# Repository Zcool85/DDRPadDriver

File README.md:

# Introduction

Projet de création d'un tapis de dance pour le jeu Dance Dance Revolution.

Ce tapis est utilisable sur un PC pour des jeux comme `Stepmania` ou `Outfox`, mais également sur
console Playstation (1 et 2).

Le firmware est à base de microcontroller AVR ©.

Les touches du tapis peuvent être illuminées. Dans ce cas, il convient d'ajouter une alimentation externe pour les LED (CAO `Power_Supply`). Cette alimentation est inutile si le tapis est utilisé sans éclairage.

## Licence

Le présent projet est sous licence MIT (Cf. [License](LICENSE.md)).

ATTENTION : Le Firmware utilise une librairie tierce V-USB pour la connexion USB vers un PC.
Cette librairie est soumie à une licnece GNU General Public License Version 2 (GPL). Merci
de consulter a license de cette bibliothèque en cas de modification.

Cf. [Librairie V-USB](https://obdev.at/products/vusb/index.html).

## Organisation du repo

Le répertoire `CAD` contient les fichiers de CAO des diférents composants :
- `Power_Supply` : Fichier CAO utilisé pour le bloc d'alimentation des tapis
- `For_Childrens` : Fichier CAO utilisé pour créer un tapis à la taille d'un enfant (~6ans)
- `For_Adults` : Fichier CAO utilisé pour créer un tapis pour adulte
- `Fonts` : Répertoire contenant les fonts utilisées par les fichiers de CAO

Le répertoire `Schematics` contient le shéma du circuit électronique du tapis.

Le répertoire `Datasheets` contient tous les datasheets des composants utilisés par le circuit électronique.

Le répertoire `Firmware` contient le code complet du firmware du microcontroller présent dans le circtui électronique.

Le répertoire `Documentation` Contient un peu de documentation permettant de comprendre comment fonctionne les trames d'une manette PS2.

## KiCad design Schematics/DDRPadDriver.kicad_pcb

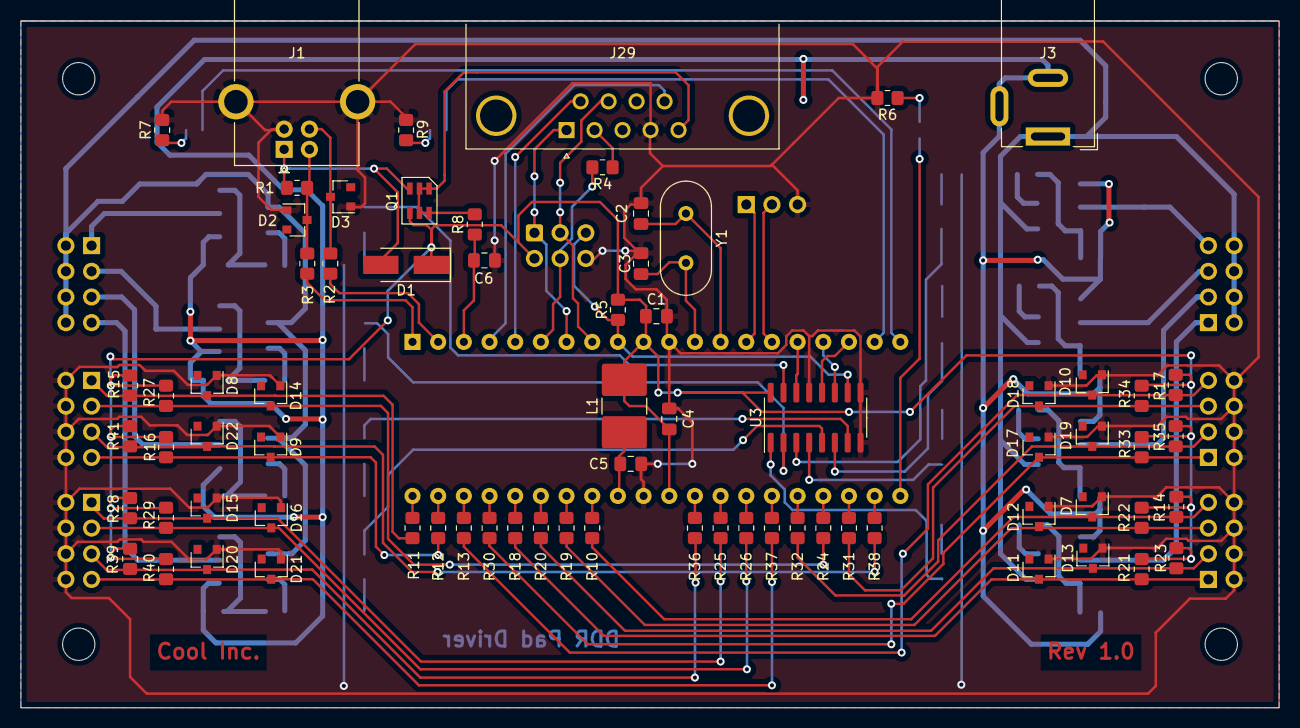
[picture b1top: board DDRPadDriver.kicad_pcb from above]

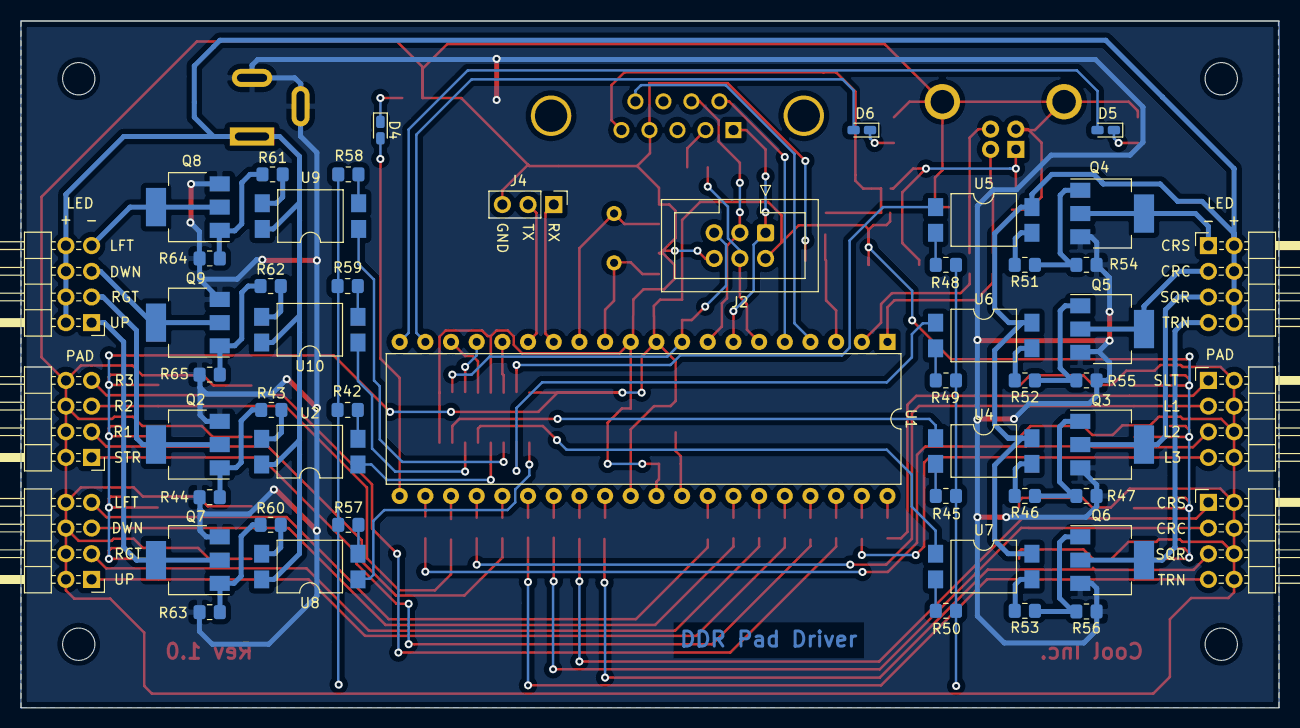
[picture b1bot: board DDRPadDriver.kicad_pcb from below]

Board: 2 copper layers, 124.5 x 67.9 mm, 129 parts (52 on the bottom side), 104 nets.

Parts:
C1: 4.7uF; C_0805_2012Metric_Pad1.18x1.45mm_HandSolder
C2, C3: 10pF; C_0805_2012Metric_Pad1.18x1.45mm_HandSolder
C4, C5, C6: 0.1uF; C_0805_2012Metric_Pad1.18x1.45mm_HandSolder
D1: SS12; D_SMA_Handsoldering
D2, D3: 3V6; D_SOT-23_ANK
D4, D5, D6: LED; LED_0603_1608Metric_Castellated
D7, D8, D9, D10, D11, D12, D13, D14, D15, D16, D17, D18, D19, D20, D21, D22: BZX84C3V6; D_SOT-23_ANK
H1, H2, H3, H4: MountingHole; MountingHole_3.2mm_M3
J1: USB_B; USB_B_OST_USB-B1HSxx_Horizontal
J2: AVR-ISP-6; IDC-Header_2x03_P2.54mm_Vertical
J3: Barrel_Jack_Switch; BarrelJack_Wuerth_6941xx301002
J4: Conn_01x03_Male; PinHeader_1x03_P2.54mm_Vertical
J5, J6, J7, J8, J9, J10: Conn_01x08_Male; PinHeader_2x04_P2.54mm_Horizontal
J29: PS2; DSUB-9_Female_Horizontal_P2.77x2.84mm_EdgePinOffset7.70mm_H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
L1: 10mH; L_2816_7142Metric_Pad3.20x4.45mm_HandSolder
Q1: PMN30XPA; TSOP-6_3pins
Q2, Q3, Q4, Q5, Q6, Q7, Q8, Q9: BCP56; SOT-223-3_TabPin2
R1: 1K5; R_0805_2012Metric_Pad1.20x1.40mm_HandSolder
R2, R3: 68; R_0805_2012Metric_Pad1.20x1.40mm_HandSolder
R4, R5, R8: 10K; R_0805_2012Metric_Pad1.20x1.40mm_HandSolder
R6, R7, R9, R10, R11, R12, R13, R18, R19, R20, R24, R25, R26, R30, R31, R32, R36, R37, R38, R42, R45, R48, R49, R50, R57, R58, R59: 470; R_0805_2012Metric_Pad1.20x1.40mm_HandSolder
R14, R15, R16, R17, R21, R22, R23, R27, R28, R29, R33, R34, R35, R39, R40, R41: 680; R_0805_2012Metric_Pad1.20x1.40mm_HandSolder
R43, R46, R51, R52, R53, R60, R61, R62: 1K; R_0805_2012Metric_Pad1.20x1.40mm_HandSolder
R44, R47, R54, R55, R56, R63, R64, R65: 4K7; R_0805_2012Metric_Pad1.20x1.40mm_HandSolder
U1: ATmega164P-20PU; DIP-40_W15.24mm
U2, U4, U5, U6, U7, U8, U9, U10: SFH620A-2X007T; SMDIP-4_W9.53mm_Clearance8mm
U3: 74HC595; SOIC-16_3.9x9.9mm_P1.27mm
Y1: 12MHz; Crystal_HC49-U_Vertical

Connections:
3V3: J29.5, Q1.3, R8.2
5V: D1.2, J1.1, Q1.1, R1.1
12V: J3.1, J9.2, J9.4, J9.6, J9.8, J10.2, J10.4, J10.6, J10.8, U2.4, U4.4, U5.4, U6.4, U7.4, U8.4, U9.4, U10.4
/B1-CROSS: R25.2, U1.28
/B2-CIRCLE: R26.2, U1.27
/B3-SQUARE: R36.2, U1.29
/B4-TRIANGLE: R37.2, U1.26
/D+: R2.2, U1.2
/D-: R3.2, U1.1
/DOWN: R19.2, U1.34
/L1: R24.2, U1.24
/L2: R38.2, U1.22
/L3: R12.2, U1.39
/LEDs/L-CIRCLE: J10.3, Q5.2
/LEDs/L-CROSS: J10.1, Q4.2
/LEDs/L-DOWN: J9.5, Q9.2
/LEDs/L-LEFT: J9.7, Q8.2
/LEDs/L-RIGHT: J9.3, Q2.2
/LEDs/L-SQUARE: J10.5, Q3.2
/LEDs/L-TRIANGLE: J10.7, Q6.2
/LEDs/L-UP: J9.1, Q7.2
/LEDs/LED-B: U3.6, U10.1
/LEDs/LED-BL: U3.5, U7.1
/LEDs/LED-BR: U3.7, U4.1
/LEDs/LED-L: U3.3, U9.1
/LEDs/LED-R: U2.1, U3.4
/LEDs/LED-U: U3.1, U8.1
/LEDs/LED-UL: U3.15, U5.1
/LEDs/LED-UR: U3.2, U6.1
/LEFT: R10.2, U1.33
/MISO: J2.1, J29.1, U1.7
/MOSI: J2.4, R4.2, U1.6
/PSX_DSR: J29.9, U1.4
/PSX_SCK: J2.3, J29.7, U1.8
/PSX_TXD: J29.2, R4.1
/Pads/C_CIRCLE: D16.1, J6.3, R26.1, R29.2
/Pads/C_CROSS: D15.1, J6.1, R25.1, R28.2
/Pads/C_DOWN: D12.1, J5.5, R19.1, R22.2
/Pads/C_L1: D14.1, J8.3, R24.1, R27.2
/Pads/C_L2: D22.1, J8.5, R38.1, R41.2
/Pads/C_L3: D9.1, J8.7, R12.1, R16.2
/Pads/C_LEFT: D7.1, J5.7, R10.1, R14.2
/Pads/C_R1: D19.1, J7.3, R32.1, R35.2
/Pads/C_R2: D18.1, J7.5, R31.1, R34.2
/Pads/C_R3: D10.1, J7.7, R13.1, R17.2
/Pads/C_RIGHT: D13.1, J5.3, R20.1, R23.2
/Pads/C_SELECT: D8.1, J8.1, R11.1, R15.2
/Pads/C_SQUARE: D20.1, J6.5, R36.1, R39.2
/Pads/C_START: D17.1, J7.1, R30.1, R33.2
/Pads/C_TRIANGLE: D21.1, J6.7, R37.1, R40.2
/Pads/C_UP: D11.1, J5.1, R18.1, R21.2
/R1: R32.2, U1.25
/R2: R31.2, U1.23
/R3: R13.2, U1.38
/RIGHT: R20.2, U1.35
/RX: J4.1, U1.14
/S1-SELECT: R11.2, U1.40
/S2-START: R30.2, U1.37
/SHIFT_CLK: U1.17, U3.11
/SHIFT_RCK: U1.18, U3.12
/SHIFT_SER: U1.16, U3.14
/TX: J4.2, U1.15
/UP: R18.2, U1.36
/~PSX_DTR~: J29.6, U1.5
/~RESET~: J2.5, R5.2, U1.9, U3.10
GND: C1.2, C2.1, C3.1, C4.2, C5.2, C6.2, D2.2, D3.2, D7.2, D8.2, D9.2, D10.2, D11.2, D12.2, D13.2, D14.2, D15.2, D16.2, D17.2, D18.2, D19.2, D20.2, D21.2, D22.2, J1.4, J1.5, J2.6, J4.3, J5.2, J5.4, J5.6, J5.8, J6.2, J6.4, J6.6, J6.8, J7.2, J7.4, J7.6, J7.8, J8.2, J8.4, J8.6, J8.8, J29.4, R6.2, R7.2, R9.2, R42.2, R45.2, R48.2, R49.2, R50.2, R57.2, R58.2, R59.2, U1.11, U1.31, U3.8, U3.9, U3.13
GND12V: J3.2, J3.3, Q2.3, Q3.3, Q4.3, Q5.3, Q6.3, Q7.3, Q8.3, Q9.3, R44.1, R47.1, R54.1, R55.1, R56.1, R63.1, R64.1, R65.1
unnamed: C2.2, U1.13, Y1.1
unnamed: C3.2, U1.12, Y1.2
unnamed: C5.1, L1.2, U1.32
unnamed: C6.1, R8.1, U1.3
unnamed: D2.1, J1.2, R1.2, R3.1
unnamed: D3.1, J1.3, R2.1
unnamed: D4.1, R6.1
unnamed: D4.2, U1.21
unnamed: D5.1, R7.1
unnamed: D5.2, U1.20
unnamed: D6.1, R9.1
unnamed: D6.2, U1.19
unnamed: Q2.1, R43.1, R44.2
unnamed: Q3.1, R46.1, R47.2
unnamed: Q4.1, R51.1, R54.2
unnamed: Q5.1, R52.1, R55.2
unnamed: Q6.1, R53.1, R56.2
unnamed: Q7.1, R60.1, R63.2
unnamed: Q8.1, R61.1, R64.2
unnamed: Q9.1, R62.1, R65.2
unnamed: R42.1, U2.2
unnamed: R43.2, U2.3
unnamed: R45.1, U4.2
unnamed: R46.2, U4.3
unnamed: R48.1, U5.2
unnamed: R49.1, U6.2
unnamed: R50.1, U7.2
unnamed: R51.2, U5.3
unnamed: R52.2, U6.3
unnamed: R53.2, U7.3
unnamed: R57.1, U8.2
unnamed: R58.1, U9.2
unnamed: R59.1, U10.2
unnamed: R60.2, U8.3
unnamed: R61.2, U9.3
unnamed: R62.2, U10.3
VCC: C1.1, C4.1, D1.1, J2.2, L1.1, Q1.2, R5.1, R14.1, R15.1, R16.1, R17.1, R21.1, R22.1, R23.1, R27.1, R28.1, R29.1, R33.1, R34.1, R35.1, R39.1, R40.1, R41.1, U1.10, U1.30, U3.16

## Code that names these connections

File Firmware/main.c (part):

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//    D- --------------- PB0 -| 1        40 |- PA0 <------------ S1-SELECT
//    D+ --------------- PB1 -| 2        39 |- PA1 <------------ L3
//    3V3 input -------> PB2 -| 3        38 |- PA2 <------------ R3
//    PSX_DSR <--Hi-Z--- PB3 -| 4        37 |- PA3 <------------ S2-START
//    PSX_DTR ---------> PB4 -| 5        36 |- PA4 <------------ UP
//    PSX_TXD ---------> PB5 -| 6        35 |- PA5 <------------ RIGHT
//    PSX_RXD <--Hi-Z--- PB6 -| 7        34 |- PA6 <------------ DOWN
//    PSX_SCK ---------> PB7 -| 8        33 |- PA7 <------------ LEFT
//                   _RESET_ -| 9        32 |- AREF
//                       VCC -| 10       31 |- GND
//                       GND -| 11       30 |- AVCC
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//                     XTAL1 -| 13       28 |- PC6 <------------ B1-CROSS
//    RX --------------> PD0 -| 14       27 |- PC5 <------------ B2-CIRCLE
//    TX <-------------- PD1 -| 15       26 |- PC4 <------------ B4-TRIANGLE
//    SHIFT_SER <------- PD2 -| 16       25 |- PC3 <------------ R1
//    SHIFT_CLK <------- PD3 -| 17       24 |- PC2 <------------ L1
//    SHIFT_RCK <------- PD4 -| 18       23 |- PC1 <------------ R2
//    LED PSX <--------- PD5 -| 19       22 |- PC0 <------------ L2
//    LED USB <--------- PD6 -| 20       21 |- PD7 ------------> LED PAD
//                             -------------
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
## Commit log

2022-03-12 Version initiale avec USB opérationnel
2022-03-12 Add hc595 support
2022-03-13 Add schematics TODOs
2022-03-13 refactoring HC595 + LED / PAD mapping
2022-03-14 Revue des pads (ajustement Zener)
2022-03-19 Communication avec a PS2 OK
2022-03-19 Un peu de ménage dans le code
2022-03-19 Refactoring code
2022-03-19 Finalisation Firmware, renommage des pins pour la PSX
2022-03-19 Toute la schematic est testé OK
2022-03-20 Ajout de ma licence V-USB
2022-03-20 Ajout d'une license MIT
2022-03-20 Réorganisation du repo
2022-04-24 Add freeCAD design for child DDR Pad
2022-04-24 Add CAD pad contacts
2022-04-24 Add CAD polycarbonate pads
2022-04-24 Add CAD CNC cut for inner pad
2022-04-24 Add schematic numerotation
2022-04-28 Ajout des empruntes des composants
2022-04-30 Add 3D models and footprints
2022-05-07 Partial routing PCB
2022-05-11 Finalisation PCB
2022-05-15 Add CAD Box pat
2022-05-17 Add START and SELECT buttons and START Job for CNC
2022-05-18 CAD : Add START and SELECT Job
2022-05-26 Add START and SELECT Job
2022-05-27 CAD : Initialize Power Supply
2022-05-27 CAD : Power Supply - Add IEC plug
2022-05-27 CAD : Power Supply - Add left side
2022-05-27 CAD : Power Supply - Add front side
2022-05-27 CAD : Power Supply - Add front aluminium profile
2022-05-27 CAD : Power Supply - Add screen printing on aluminium profile
2022-05-28 CAD : Add milling wood cuts
2022-05-29 CAD : Add Aluminium profile job for power supply and test screen printing
2022-05-29 CAD : Add reenforcements to LittleDancePad
2022-06-06 CAD : Finalize panels for Children pad and power supply
2022-06-06 Correction README.md
2022-06-06 Change uC to ATmega164p-20PU
2022-06-11 CAD : Initialize adult DDR pad
2022-06-26 CAD : Add supports
2026-04-19 Fix typo in project description in README.md Add *.FCBak to .gitignore
2026-04-19 Add documentation for DualShock 2 frame and include related images
2026-04-19 Cleanup CAD directory and upgrade to FreeCAD 1.1.1
2026-04-19 Stable version

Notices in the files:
Firmware/main.c:
@copyright Copyright © 2022 Zéro Cool
